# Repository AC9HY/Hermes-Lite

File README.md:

Hermes-Lite
===========

This fork is no loger being updated. The amplifers are now at https://github.com/W9JSW

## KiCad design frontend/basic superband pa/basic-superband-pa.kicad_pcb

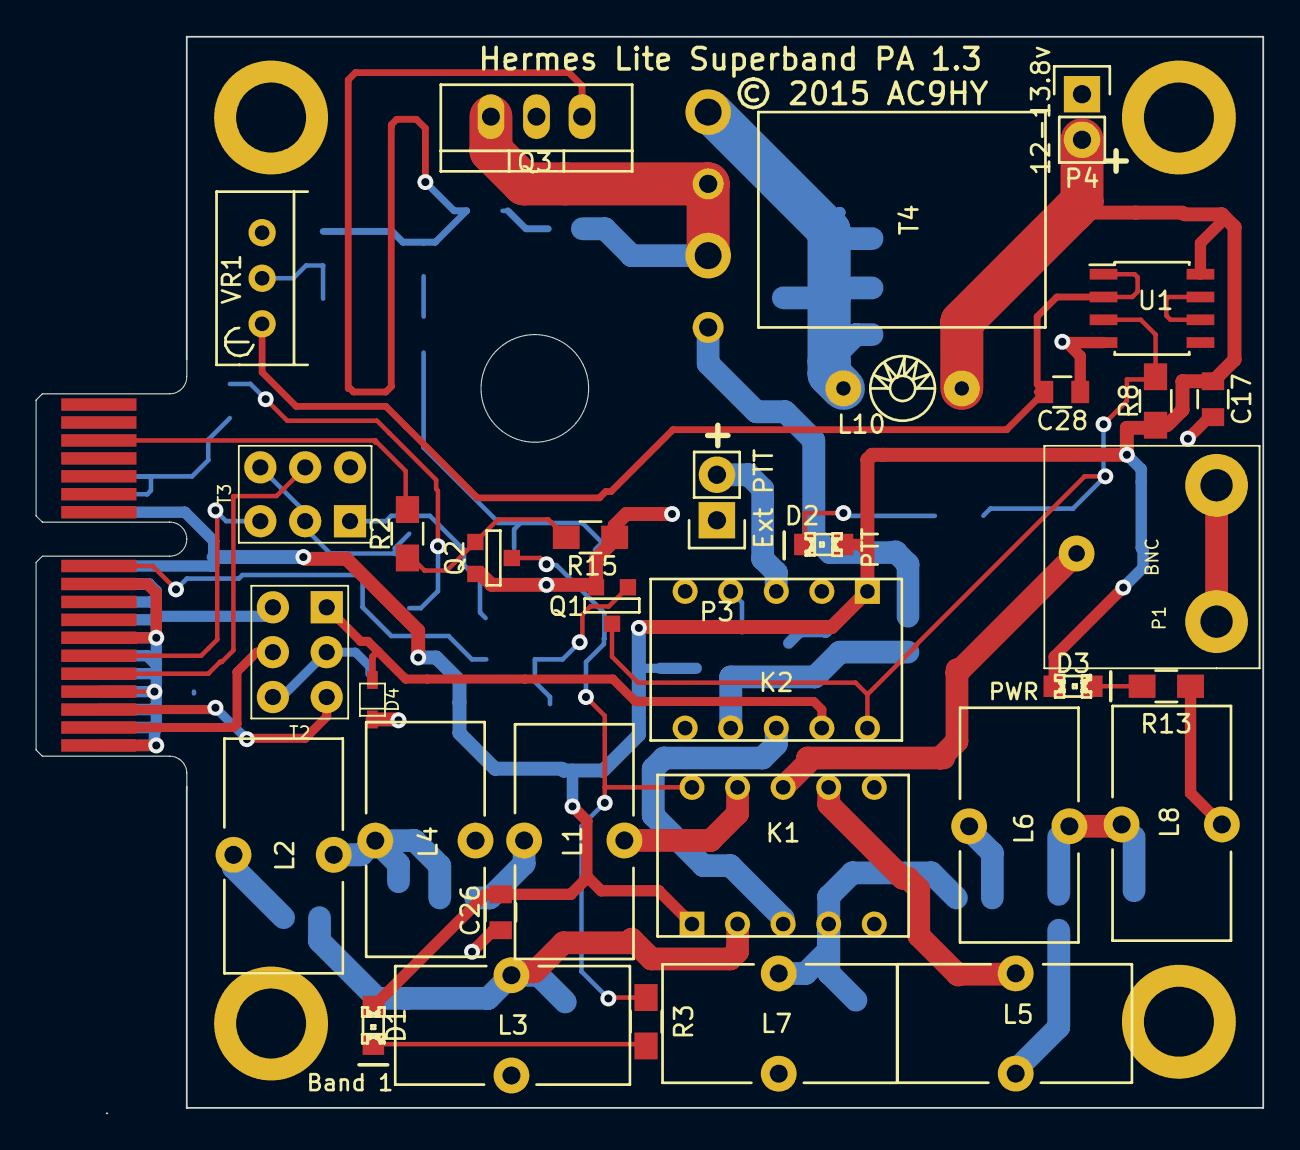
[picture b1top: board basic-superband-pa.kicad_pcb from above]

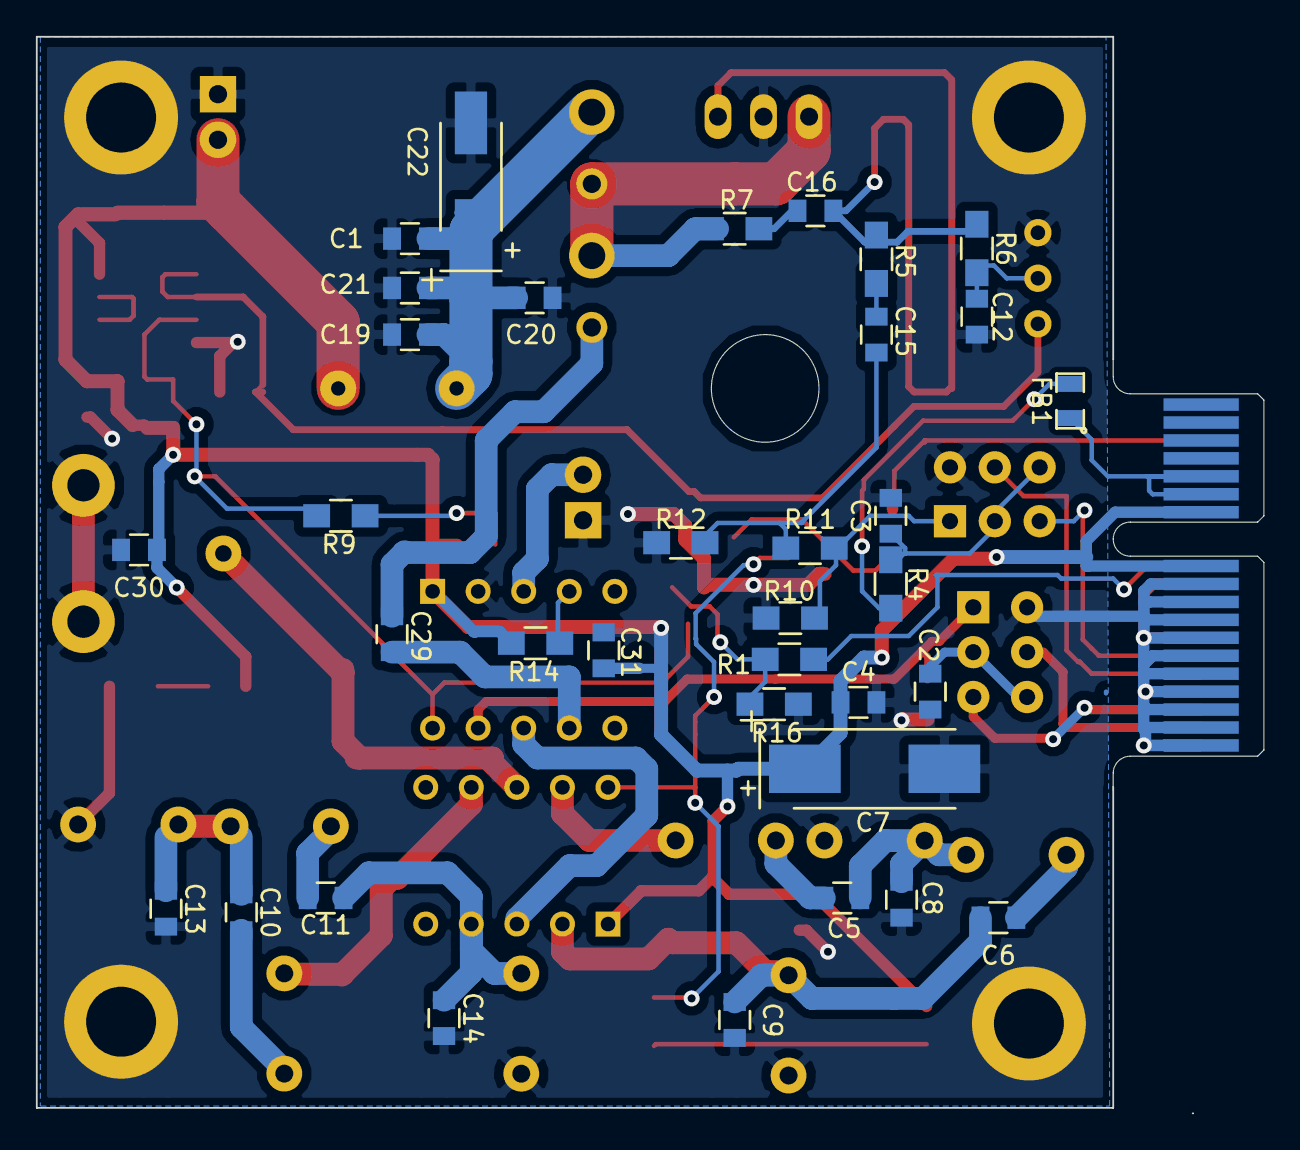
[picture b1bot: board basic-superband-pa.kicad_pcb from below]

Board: 2 copper layers, 68.4 x 59.7 mm, 75 parts (36 on the bottom side), 46 nets.

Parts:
C1, C4, C12, C15, C16, C19, C20, C26, C29, C30, C31: 0.1uF; C_0805
C2, C3: 0.1 uF; C_0805
C5, C6, C8, C9, C10, C11, C13, C14: C; C_0805
C7: 47uF 25V; TantalC_SizeD_EIA-7343_HandSoldering
C17, C28: 1uF; C_0805
C21: 4700pF; C_0805
C22: 10uF 25V; TantalC_SizeC_EIA-6032_HandSoldering
CN1: EDGE
D1: YEL LED (Band1); LED-0805
D2: RED LED (PTT); LED-0805
D3: GRN LED (PWR ON); LED-0805
D4: DIODESCH2; SOD323
FB1: FB; SMD-0805
K1, K2: D3002
L1, L2, L3, L4, L5, L6, L7, L8: INDUCTOR; Choke_Toroid_6,5x13mm_Vertical
L10: FT37-43 11T #26; Choke_Toroid_horizontal_Diameter3-5mm_Amidon-T12
MH: VAL**; MH
MH#2, MH#3, MH#4: VAL**; MH
MountingHole_6mm: VAL**; MountingHole_6mm
P1: BNC; BNCRA
P3: Ext PTT; Pin_Header_Straight_1x02
P4: 12-13.8v; Pin_Header_Straight_1x02
Q1, Q2: FDV301; SOT-23-GDS
Q3: RD16HHF1; TO-220_Neutral123_Vertical
R1, R2: 499; R_0805_HandSoldering
R3, R9, R13, R14: 4.99k; R_0805_HandSoldering
R4: 0; R_0805_HandSoldering
R5: 6.8; R_0805_HandSoldering
R6, R8, R15, R16: 10k; R_0805_HandSoldering
R7, R10, R12: 270; R_0805_HandSoldering
R11: 18; R_0805_HandSoldering
T2: 8:1; TRANSF
T3: 4:1; TRANSF
T4: OUT_TRANSF
U1: LP2951-50D; SOIC-8_3.9x4.9mm_Pitch1.27mm
VR1: 1k MT; Potentiometer_Bourns_3296W_3-8Zoll_Inline_ScrewUp

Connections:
/PTT: K2.10, Q1.D, R8.1, R9.1, U1.3
BAND1: K1.10, Q2.D, R3.1
GND: C1.1, C2.2, C3.2, C4.2, C7.2, C8.2, C9.2, C12.1, C13.2, C14.2, C17.2, C19.1, C20.1, C21.1, C22.2, C26.1, C28.1, C30.2, C31.2, CN1.A1, CN1.A2, CN1.A3, CN1.A4, CN1.A5, CN1.A6, CN1.A7, CN1.A8, CN1.A9, CN1.A10, CN1.B1, CN1.B4, CN1.B7, CN1.B10, D4.2, K2.2, L3.2, L4.2, L7.2, L8.2, P1.2, P3.1, P4.1, Q1.S, Q2.S, Q3.2, R10.1, R12.1, R13.1, R15.1, R16.1, T2.2, T3.2, U1.4, VR1.3
unnamed: C1.2, C19.2, C20.2, C21.2, C22.1, L10.2, T4.1
unnamed: C2.1, T2.3, T2.6
unnamed: C3.1, R4.1, T3.3, T3.6
unnamed: C5.1, L1.2
unnamed: C5.2, C8.1, L2.1, L4.1
unnamed: C6.1, L2.2
unnamed: C6.2, C9.1, K1.2, L3.1
unnamed: C10.1, C13.1, L6.2, L8.1
unnamed: C10.2, L5.1
unnamed: C11.1, C14.1, K1.4, L7.1
unnamed: C11.2, L6.1
unnamed: C12.2, R6.2, VR1.2
unnamed: C15.1, R5.2
unnamed: C15.2, R11.1, R12.2
unnamed: C16.1, R7.2
unnamed: C16.2, Q3.1, R5.1, R6.1
unnamed: C4.1, C7.1, C17.1, C26.2, C30.1, C31.1, CN1.A11, CN1.A12, D1.1, D2.1, D3.1, K1.1, K2.1, L10.1, P4.2, R8.2, R14.2, U1.8
unnamed: C28.2, U1.1, U1.2, VR1.1
unnamed: C29.1, K2.7
unnamed: C29.2, T4.4
unnamed: CN1.A13, CN1.A14, FB1.1
unnamed: CN1.B2, T2.4
unnamed: CN1.B3, T2.5
unnamed: CN1.B5, T3.4
unnamed: CN1.B6, T3.5
unnamed: D1.2, R3.2
unnamed: D2.2, R9.2
unnamed: D3.2, R13.2
unnamed: D4.1, K2.9, T2.1
unnamed: FB1.2, R4.2
unnamed: K1.3, K2.8
unnamed: K1.7, L5.2
unnamed: K1.8, P1.1
unnamed: K1.9, L1.1
unnamed: K2.3, P3.2
unnamed: K2.4, R14.1
unnamed: Q1.G, R1.1, R16.2
unnamed: Q2.G, R2.1, R15.2
unnamed: Q3.3, R7.1, T4.2, T4.3
unnamed: R10.2, R11.2, T3.1
unnamed: U1.6, U1.7
PTT: CN1.B11, R1.2
USEROUT4: CN1.B16, R2.2

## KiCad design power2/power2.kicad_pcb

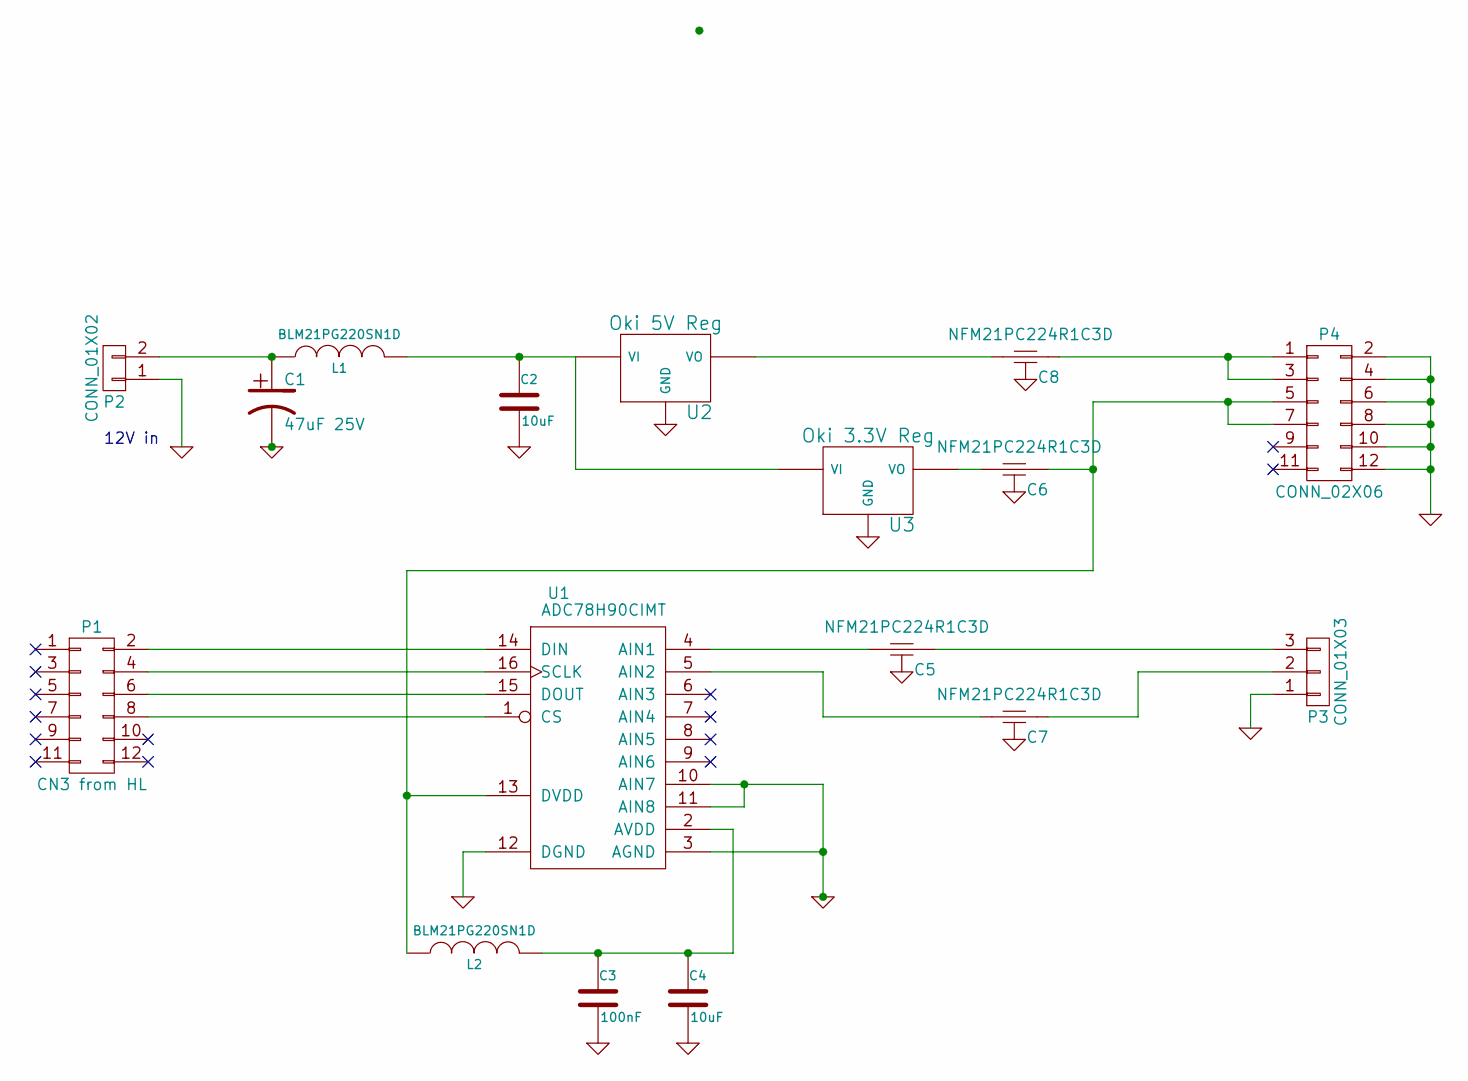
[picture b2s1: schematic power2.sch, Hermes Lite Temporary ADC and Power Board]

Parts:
C1: 47uF 25V; TantalC_SizeC_EIA-6032_HandSoldering
C2, C4: 10uF; C_0805_HandSoldering
C3: 100nF; C_0805_HandSoldering
C5, C6, C7, C8: NFM21PC224R1C3D; cfeed_0805
L1, L2: BLM21PG220SN1D; SMD-0805
P1: CN3 from HL; Socket_Strip_Angled_2x06
P2: CONN_01X02; Pin_Header_Straight_1x02
P3: CONN_01X03; Pin_Header_Straight_1x03
P4: CONN_02X06; Socket_Strip_Angled_2x06
U1: ADC78H90CIMT; SOIC-16_3.9x9.9mm_Pitch1.27mm
U2: Oki 5V Reg; LM78XXV
U3: Oki 3.3V Reg; LM78XXV

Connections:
GND: C1.2, C2.2, C3.2, C4.2, C5.3, C6.3, C7.3, C8.3, P2.1, P3.1, P4.2, P4.4, P4.6, P4.8, P4.10, P4.12, U1.3 (AGND), U1.10 (AIN7), U1.11 (AIN8), U1.12 (DGND), U2.GND, U3.GND; also elsewhere on the board
unnamed: C1.1, L1.1, P2.2
unnamed: C2.1, L1.2, U2.VI, U3.VI
unnamed: C3.1, C4.1, L2.2, U1.2 (AVDD)
unnamed: C5.1, U1.4 (AIN1)
unnamed: C5.2, P3.3
unnamed: C6.1, U3.VO
unnamed: C6.2, L2.1, P4.5, P4.7, U1.13 (DVDD)
unnamed: C7.1, U1.5 (AIN2)
unnamed: C7.2, P3.2
unnamed: C8.1, U2.VO
unnamed: C8.2, P4.1, P4.3
unnamed: P1.2, U1.14 (DIN)
unnamed: P1.4, U1.16 (SCLK)
unnamed: P1.6, U1.15 (DOUT)
unnamed: P1.8, U1.1 (CS)

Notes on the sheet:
12V in

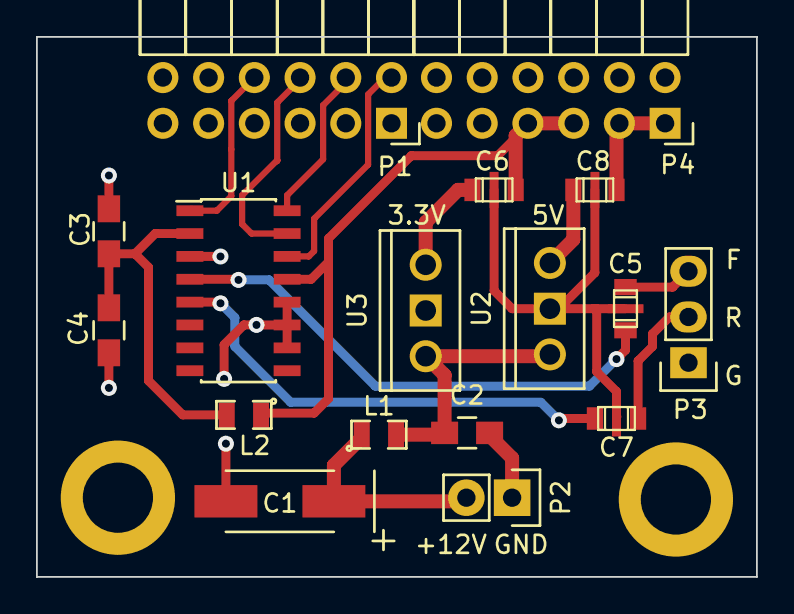
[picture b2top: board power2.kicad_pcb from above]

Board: 2 copper layers, 40.0 x 30.0 mm, 19 parts (0 on the bottom side), 16 nets.

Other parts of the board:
MH: VAL**; MH
MH#2: VAL**; MH

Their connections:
GND: MH.2, MH#2.1; also elsewhere on the board

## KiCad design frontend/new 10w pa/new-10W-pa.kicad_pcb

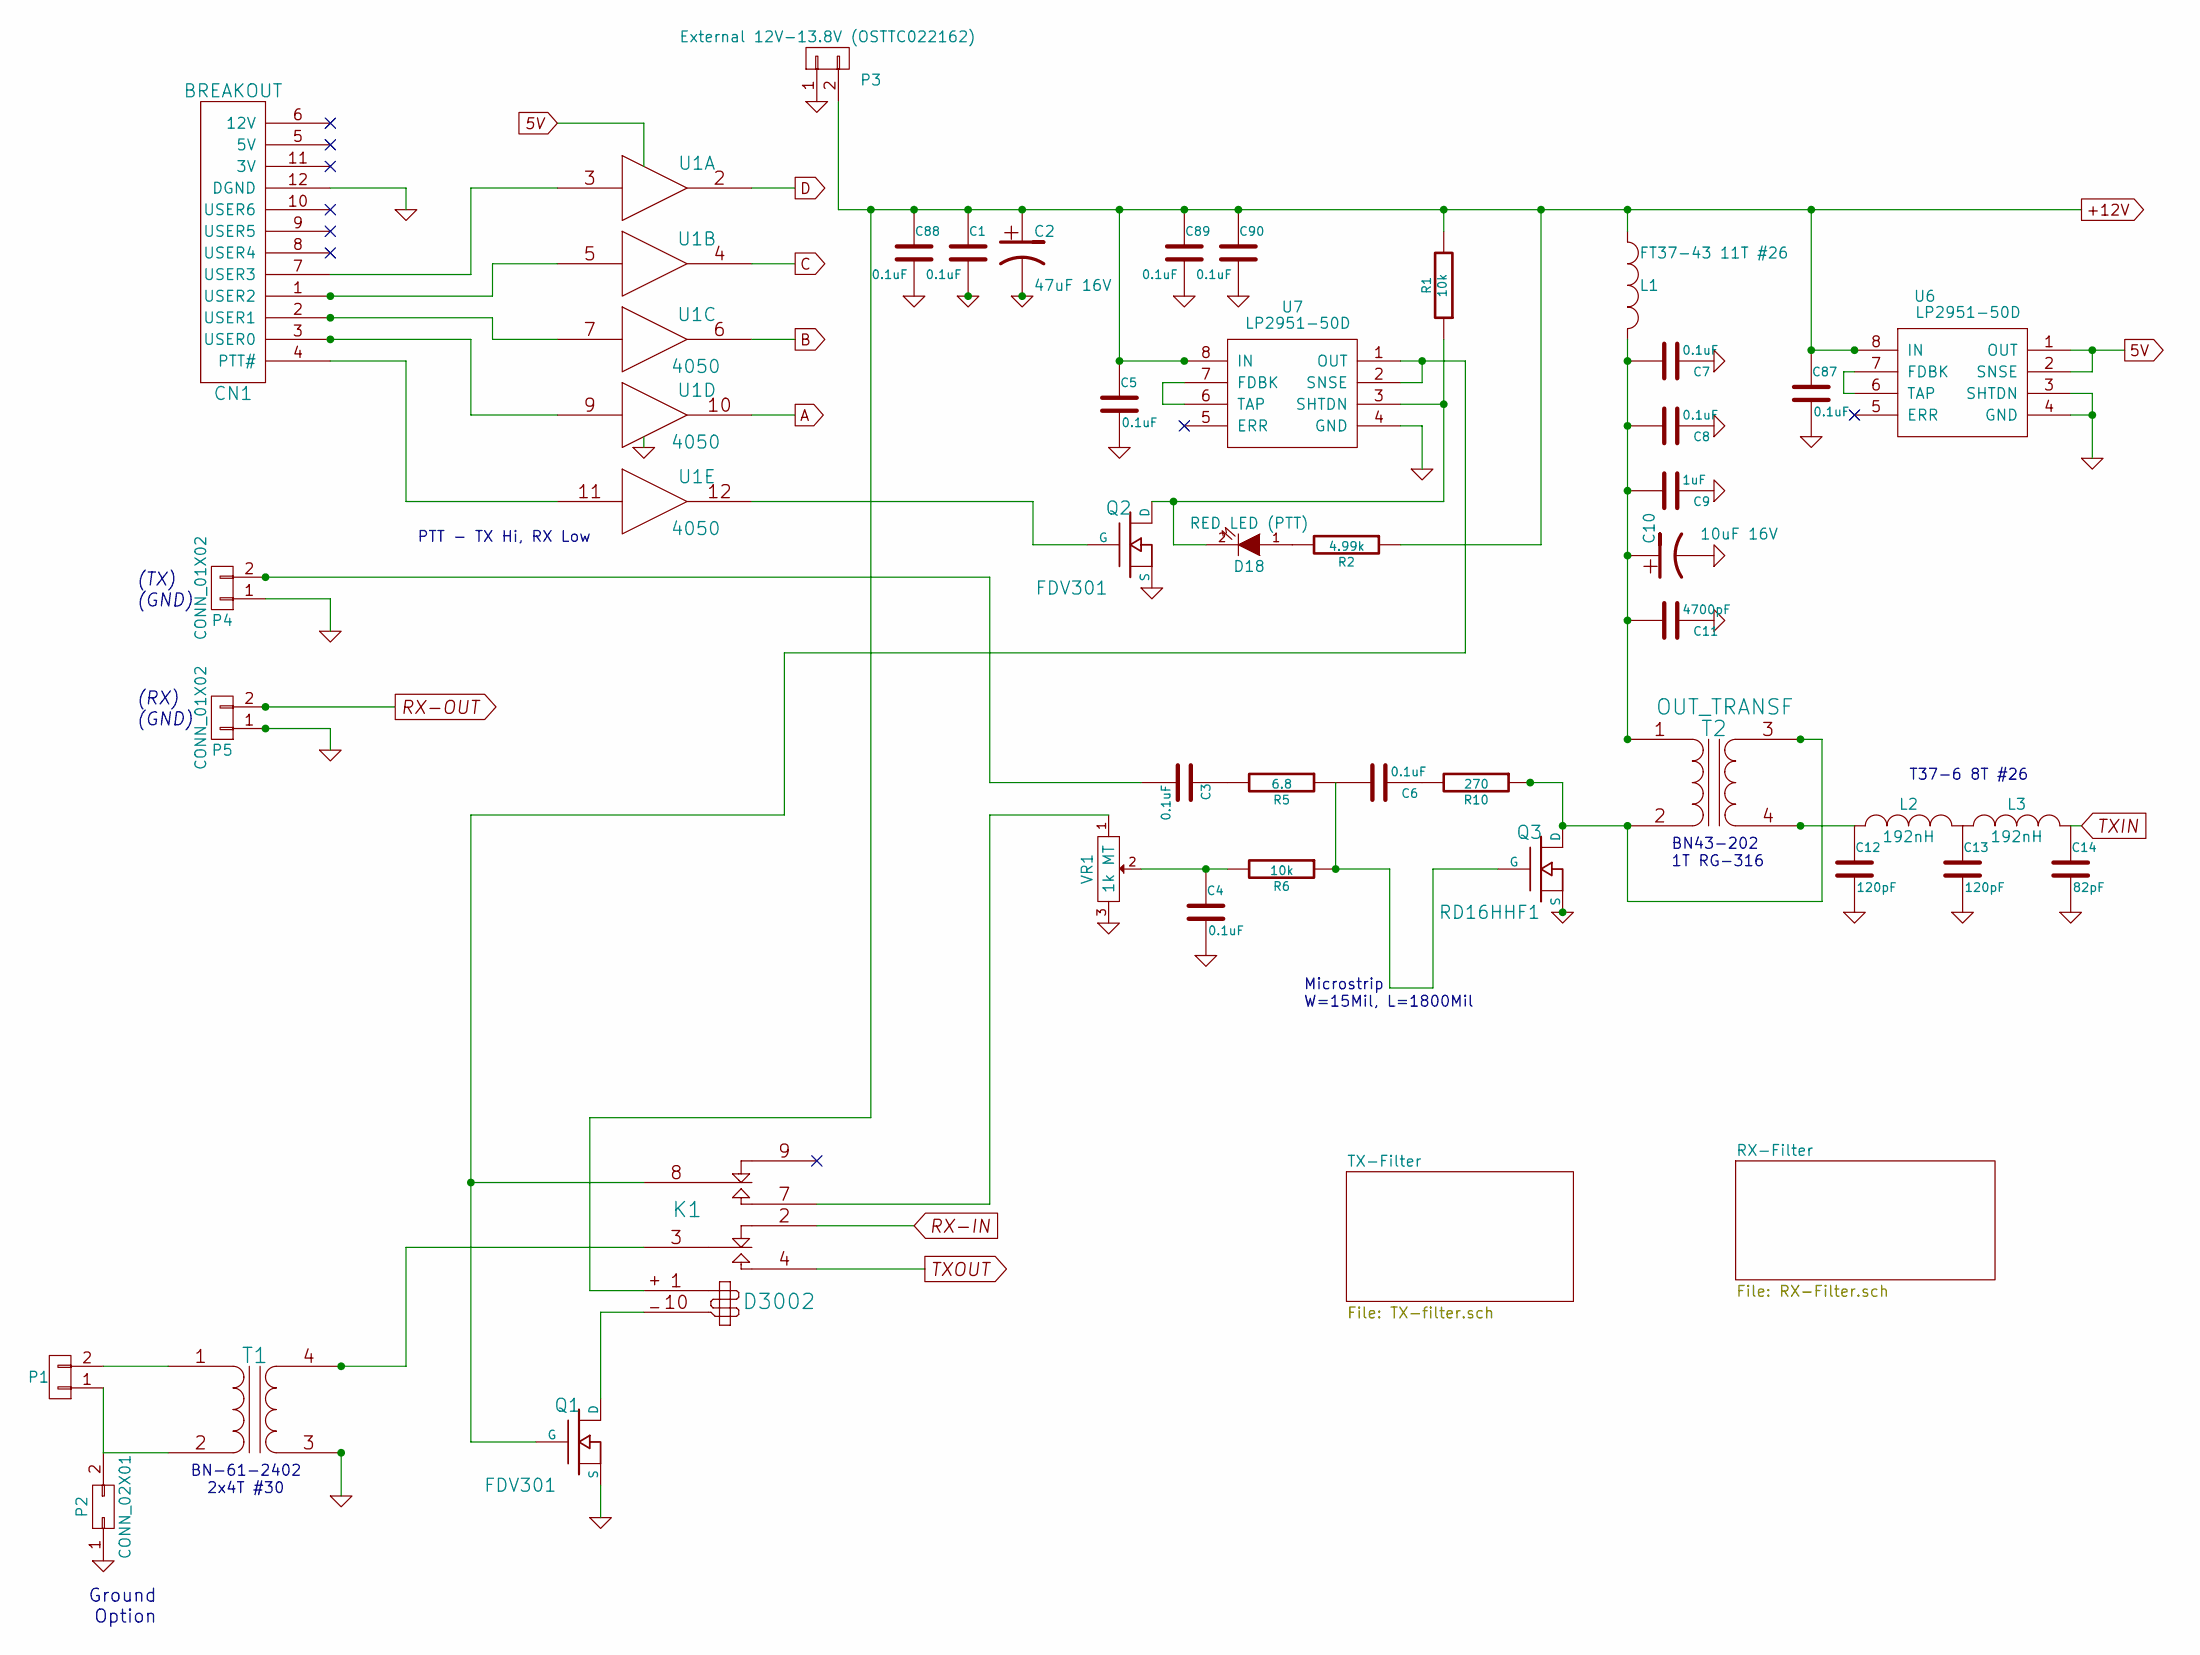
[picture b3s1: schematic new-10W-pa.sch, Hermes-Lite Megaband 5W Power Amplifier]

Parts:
C1, C3, C4, C5, C6, C7, C8, C87, C88, C89, C90: 0.1uF; C_0805
C2: 47uF 16V; TantalC_SizeD_EIA-7343_Reflow
C9: 1uF; C_0805
C10: 10uF 16V; TantalC_SizeB_EIA-3528_Reflow
C11: 4700pF; C_0805
C12, C13: 120pF; C_0805
C14: 82pF; C_0805
CN1: BREAKOUT
D18: RED LED (PTT); LED-0805
K1: D3002
L1: FT37-43 11T #26; Choke_Horizontal_RM10mm
L2, L3: 192nH; Choke_Toroid_6,5x13mm_Vertical
P1, P4, P5: CONN_01X02; Pin_Header_Straight_1x02
P2: CONN_02X01; Pin_Header_Straight_1x02
P3: External 12V-13.8V (OSTTC022162); AK300-2
Q1, Q2: FDV301; SOT-23-GDS
Q3: RD16HHF1; TO-220_Neutral123_Vertical_LargePads
R1, R6: 10k; R_0805
R2: 4.99k; R_0805
R5: 6.8; R_0805
R10: 270; R_0805
T1: TRANSFO; Socket_Strip_Straight_2x02
T2: OUT_TRANSF
U1: 4050; SOIC-16_3.9x9.9mm_Pitch1.27mm
U6, U7: LP2951-50D; SOIC-8_3.9x4.9mm_Pitch1.27mm
VR1: 1k MT; Potentiometer_Bourns_3296W_3-8Zoll_Inline_ScrewUp

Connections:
5V: U1.1 (VCC), U6.1 (OUT), U6.2 (SNSE); also elsewhere on the board
+12V: C1.1, C2.1, C5.1, C87.1, C88.1, C89.1, C90.1, K1.1 (+), L1.1, P3.2, R1.2, R2.1, U6.8 (IN), U7.8 (IN); also elsewhere on the board
A: U1.10; also elsewhere on the board
B: U1.6; also elsewhere on the board
C: U1.4; also elsewhere on the board
D: U1.2; also elsewhere on the board
unnamed: C3.1, R5.2
unnamed: C3.2, P4.2
unnamed: C4.1, R6.2, VR1.2
unnamed: C6.1, R10.2
unnamed: C6.2, Q3.1 (G), R5.1, R6.1
unnamed: C7.2, C8.2, C9.2, C10.1, C11.2, L1.2, T2.1 (AA)
unnamed: C12.1, L2.2, T2.4 (SA)
unnamed: C13.1, L2.1, L3.2
unnamed: CN1.1 (USER2), U1.5
unnamed: CN1.2 (USER1), U1.7
unnamed: CN1.3 (USER0), U1.9
unnamed: CN1.4 (PTT#), U1.11
unnamed: CN1.7 (USER3), U1.3
unnamed: D18.1 (A), R2.2
unnamed: D18.2 (K), Q2.D, R1.1, U7.3 (SHTDN)
unnamed: K1.3 (C1), T1.4 (SB)
unnamed: K1.7 (T2), VR1.1
unnamed: K1.8 (C2), Q1.G, U7.1 (OUT), U7.2 (SNSE)
unnamed: K1.10 (-), Q1.D
unnamed: P1.1, P2.2, T1.2 (AB)
unnamed: P1.2, T1.1 (AA)
unnamed: Q2.G, U1.12
unnamed: Q3.3 (D), R10.1, T2.2 (AB), T2.3 (SB)
unnamed: U6.6 (TAP), U6.7 (FDBK)
unnamed: U7.6 (TAP), U7.7 (FDBK)
RX-IN: K1.2 (R1); also elsewhere on the board
RX-OUT: P5.2; also elsewhere on the board
TXIN: C14.1, L3.1; also elsewhere on the board
TXOUT: K1.4 (T1); also elsewhere on the board
VSS: C1.2, C2.2, C4.2, C5.2, C7.1, C8.1, C9.1, C10.2, C11.1, C12.2, C13.2, C14.2, C87.2, C88.2, C89.2, C90.2, CN1.12 (DGND), P2.1, P3.1, P4.1, P5.1, Q1.S, Q2.S, Q3.2 (S), T1.3 (SA), U1.8 (VSS), U6.3 (SHTDN), U6.4 (GND), U7.4 (GND), VR1.3; also elsewhere on the board

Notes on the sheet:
Ground Option
BN-61-2402 2x4T #30
BN43-202 1T RG-316
(TX) (GND)
(RX) (GND)
T37-6 8T #26
Microstrip W=15Mil, L=1800Mil
PTT - TX Hi, RX Low

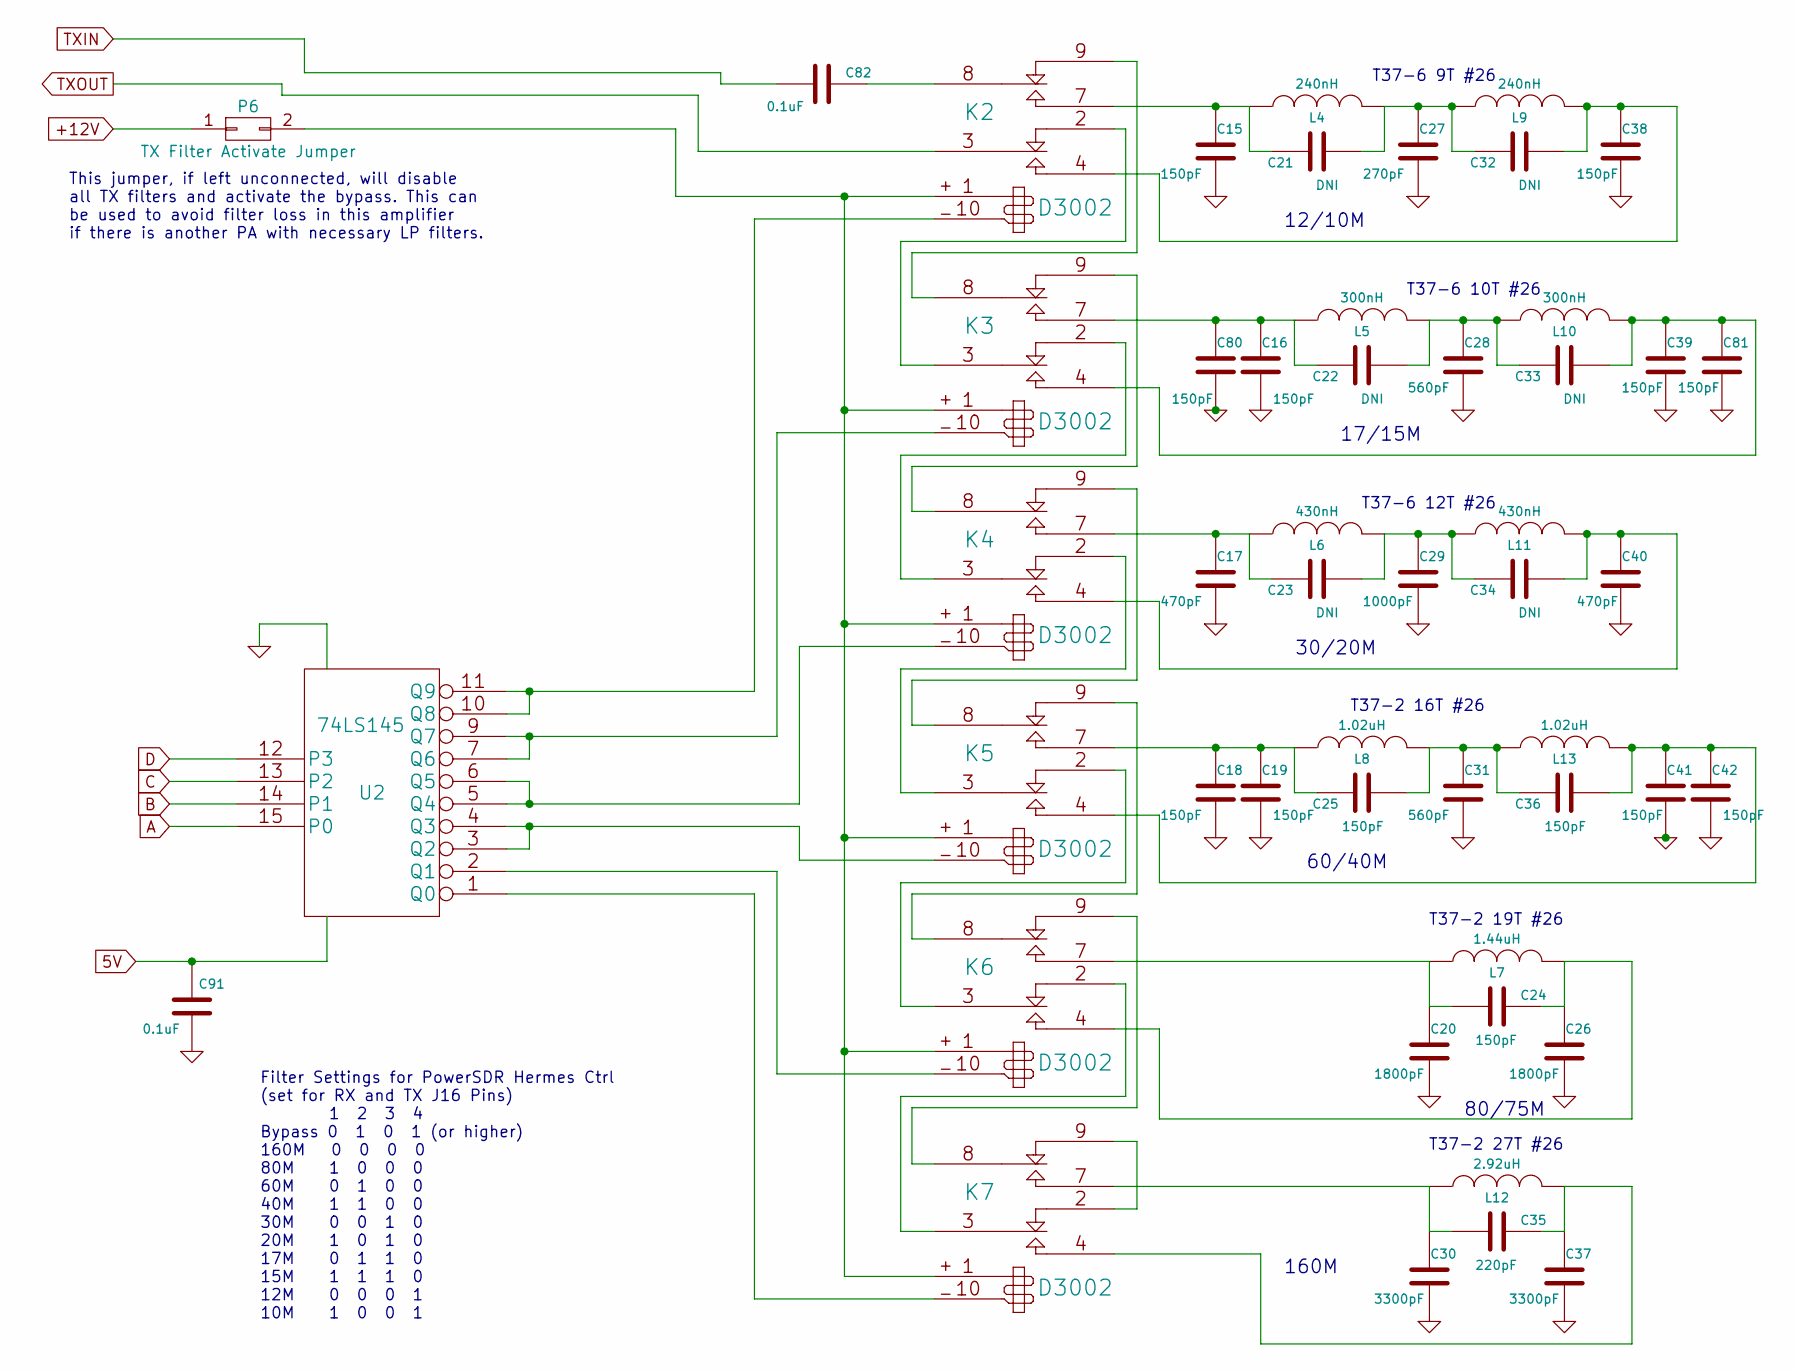
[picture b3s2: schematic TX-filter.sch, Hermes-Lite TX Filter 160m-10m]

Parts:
C15, C16, C18, C19, C24, C25, C36, C38, C39, C41, C42, C80, C81: 150pF; C_0805
C17, C40: 470pF; C_0805
C20, C26: 1800pF; C_0805
C21, C22, C23, C32, C33, C34: DNI; C_0805
C27: 270pF; C_0805
C28, C31: 560pF; C_0805
C29: 1000pF; C_0805
C30, C37: 3300pF; C_0805
C35: 220pF; C_0805
C82, C91: 0.1uF; C_0805
K2, K3, K4, K5, K6, K7: D3002
L4, L9: 240nH; Choke_Toroid_6,5x13mm_Vertical
L5, L10: 300nH; Choke_Toroid_6,5x13mm_Vertical
L6, L11: 430nH; Choke_Toroid_6,5x13mm_Vertical
L7: 1.44uH; Choke_Toroid_6,5x13mm_Vertical
L8, L13: 1.02uH; Choke_Toroid_6,5x13mm_Vertical
L12: 2.92uH; Choke_Toroid_6,5x13mm_Vertical
P6: TX Filter Activate Jumper; Pin_Header_Straight_1x02
U2: 74LS145; SOIC-16_3.9x9.9mm_Pitch1.27mm

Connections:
5V: C91.2, U2.16 (VCC); also elsewhere on the board
+12V: P6.1; also elsewhere on the board
A: U2.15 (P0); also elsewhere on the board
B: U2.14 (P1); also elsewhere on the board
C: U2.13 (P2); also elsewhere on the board
D: U2.12 (P3); also elsewhere on the board
unnamed: C15.1, C21.1, K2.7 (T2), L4.1
unnamed: C16.1, C22.1, C80.1, K3.7 (T2), L5.1
unnamed: C17.1, C23.1, K4.7 (T2), L6.1
unnamed: C18.1, C19.1, C25.1, K5.7 (T2), L8.1
unnamed: C20.1, C24.2, K6.7 (T2), L7.1
unnamed: C21.2, C27.1, C32.1, L4.2, L9.1
unnamed: C22.2, C28.1, C33.1, L5.2, L10.1
unnamed: C23.2, C29.1, C34.1, L6.2, L11.1
unnamed: C24.1, C26.1, K6.4 (T1), L7.2
unnamed: C25.2, C31.1, C36.1, L8.2, L13.1
unnamed: C30.1, C35.2, K7.7 (T2), L12.1
unnamed: C32.2, C38.1, K2.4 (T1), L9.2
unnamed: C33.2, C39.1, C81.1, K3.4 (T1), L10.2
unnamed: C34.2, C40.1, K4.4 (T1), L11.2
unnamed: C35.1, C37.1, K7.4 (T1), L12.2
unnamed: C36.2, C41.1, C42.1, K5.4 (T1), L13.2
unnamed: C82.1, K2.8 (C2)
unnamed: K2.1 (+), K3.1 (+), K4.1 (+), K5.1 (+), K6.1 (+), K7.1 (+), P6.2
unnamed: K2.2 (R1), K3.3 (C1)
unnamed: K2.9 (R2), K3.8 (C2)
unnamed: K2.10 (-), U2.10 (Q8), U2.11 (Q9)
unnamed: K3.2 (R1), K4.3 (C1)
unnamed: K3.9 (R2), K4.8 (C2)
unnamed: K3.10 (-), U2.7 (Q6), U2.9 (Q7)
unnamed: K4.2 (R1), K5.3 (C1)
unnamed: K4.9 (R2), K5.8 (C2)
unnamed: K4.10 (-), U2.5 (Q4), U2.6 (Q5)
unnamed: K5.2 (R1), K6.3 (C1)
unnamed: K5.9 (R2), K6.8 (C2)
unnamed: K5.10 (-), U2.3 (Q2), U2.4 (Q3)
unnamed: K6.2 (R1), K7.3 (C1)
unnamed: K6.9 (R2), K7.8 (C2)
unnamed: K6.10 (-), U2.2 (Q1)
unnamed: K7.2 (R1), K7.9 (R2)
unnamed: K7.10 (-), U2.1 (Q0)
TXIN: C82.2; also elsewhere on the board
TXOUT: K2.3 (C1); also elsewhere on the board
VSS: C15.2, C16.2, C17.2, C18.2, C19.2, C20.2, C26.2, C27.2, C28.2, C29.2, C30.2, C31.2, C37.2, C38.2, C39.2, C40.2, C41.2, C42.2, C80.2, C81.2, C91.1, U2.8 (GND); also elsewhere on the board

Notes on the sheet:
160M
60/40M
80/75M
T37-2 16T #26
T37-2 19T #26
T37-2 27T #26
30/20M
T37-6 12T #26
17/15M
T37-6 10T #26
12/10M
T37-6 9T #26
Filter Settings for PowerSDR Hermes Ctrl (set for RX and TX J16 Pins) 1 2 3 4 Bypass 0 1 0 1 (or higher) 160M 0 0 0 0 80M 1 0 0 0 60M 0 1 0 0 40M 1 1 0 0 30M 0 0 1 0 20M 1 0 1 0 17M 0 1 1 0 15M 1 1 1 0 12M 0 0 0 1 10M 1 0 0 1
This jumper, if left unconnected, will disable all TX filters and activate the bypass. This can be used to avoid filter loss in this amplifier if there is another PA with necessary LP filters.

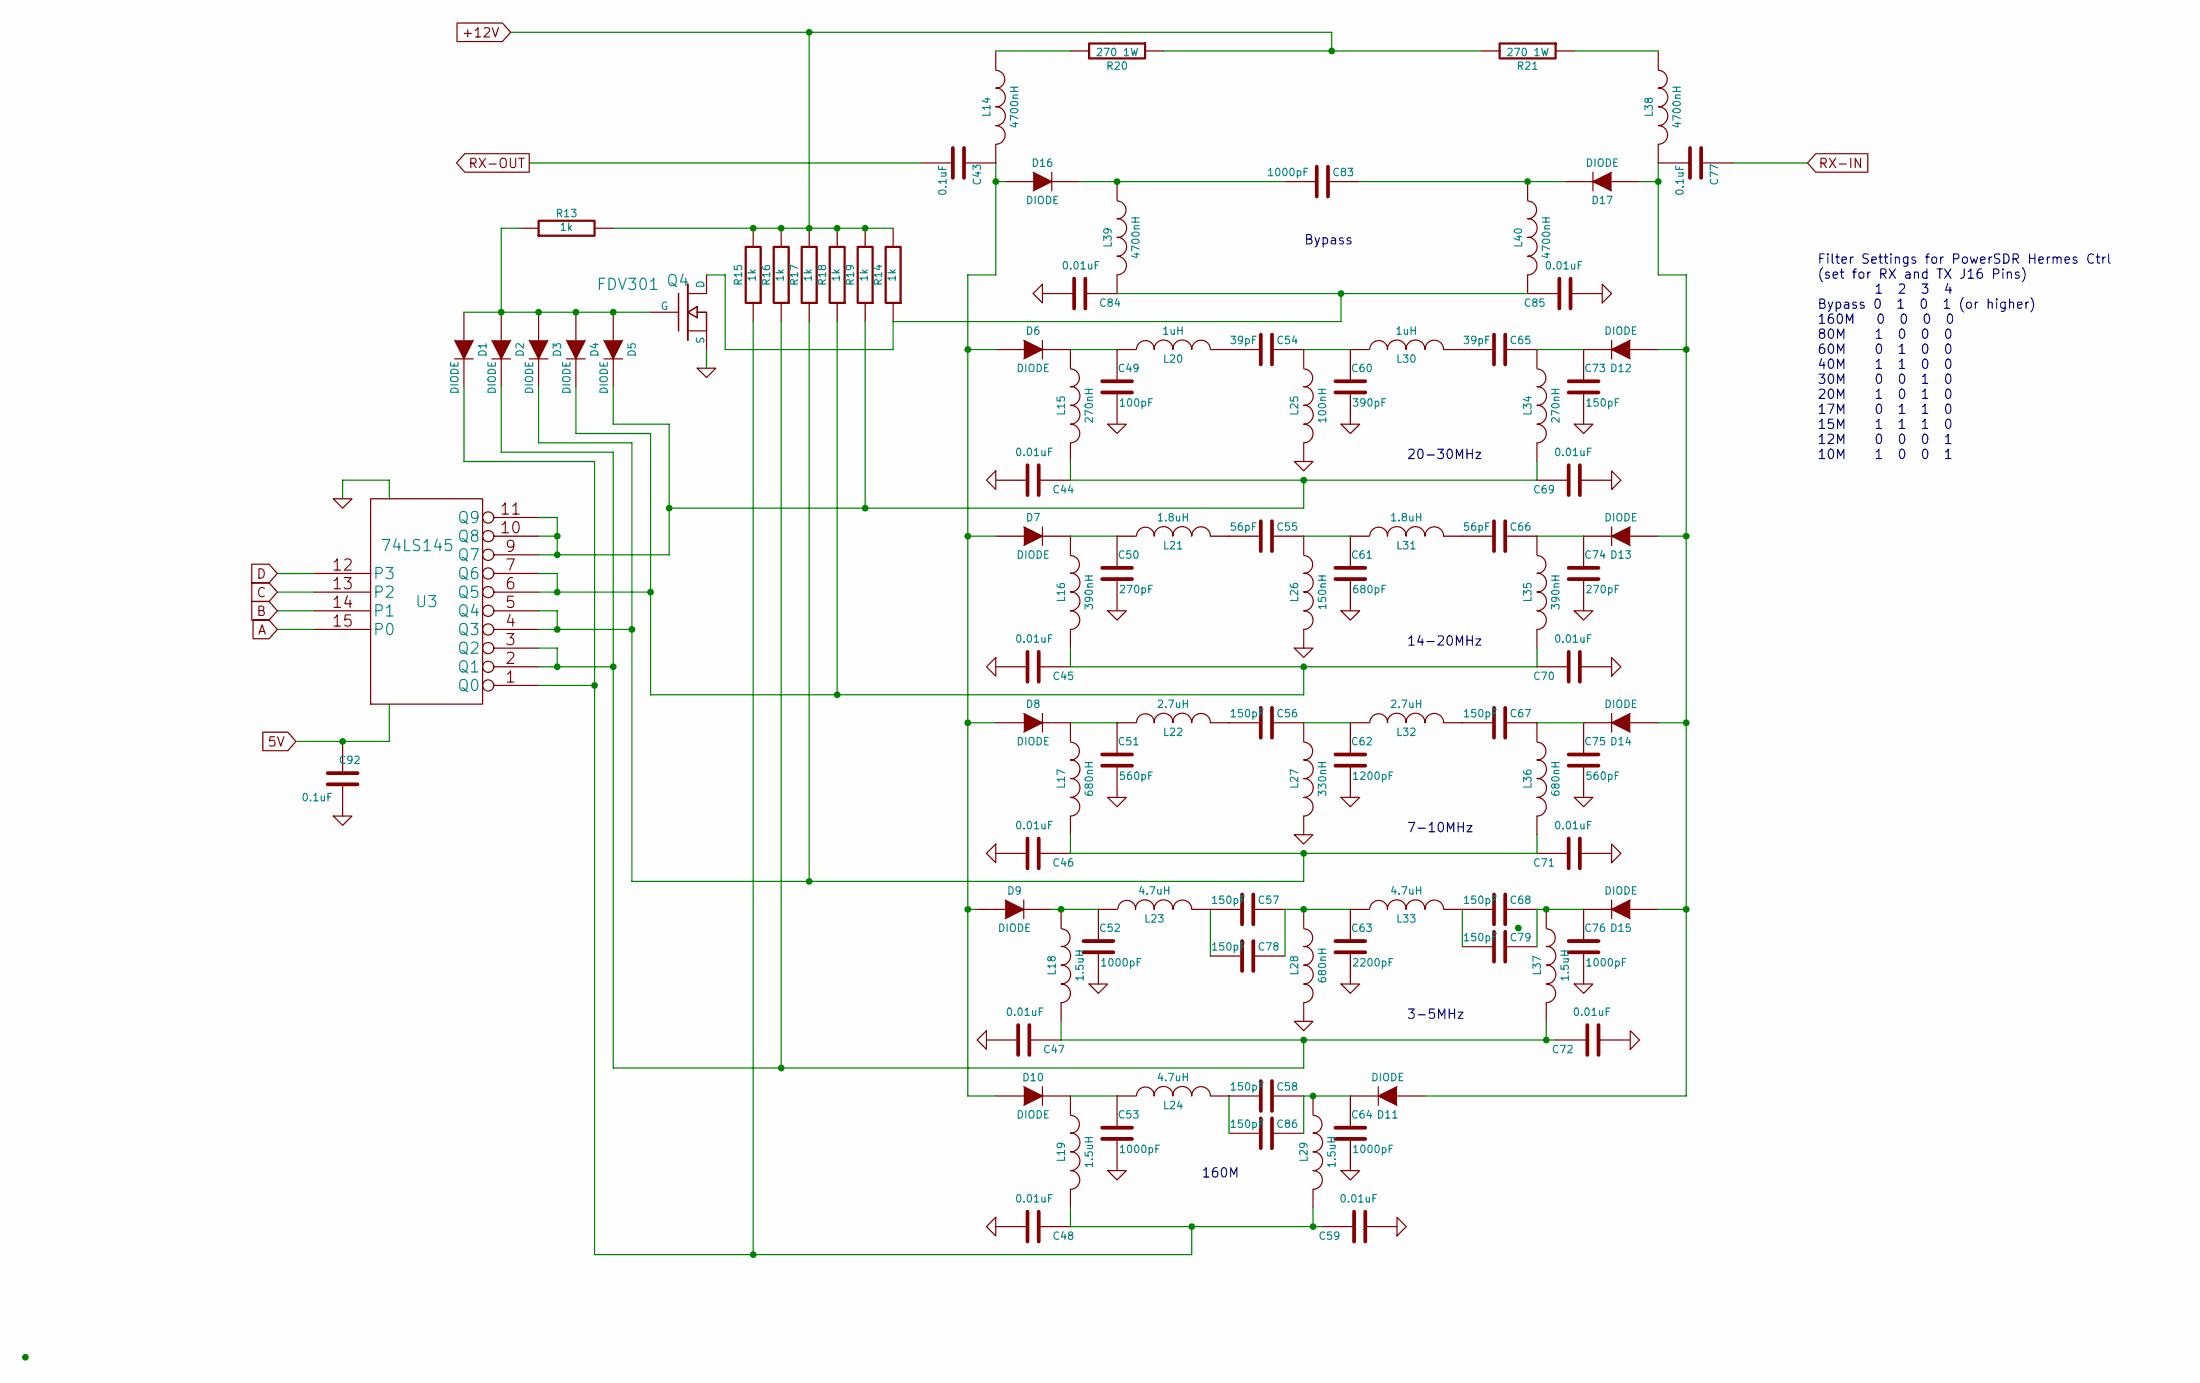
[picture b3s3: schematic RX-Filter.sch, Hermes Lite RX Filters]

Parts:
C43, C77, C92: 0.1uF; C_0805
C44, C45, C46, C47, C48, C59, C69, C70, C71, C72, C84, C85: 0.01uF; C_0805
C49: 100pF; C_0805
C50, C74: 270pF; C_0805
C51, C75: 560pF; C_0805
C52, C53, C64, C76, C83: 1000pF; C_0805
C54, C65: 39pF; C_0805
C55, C66: 56pF; C_0805
C56, C57, C58, C67, C68, C73, C78, C79, C86: 150pF; C_0805
C60: 390pF; C_0805
C61: 680pF; C_0805
C62: 1200pF; C_0805
C63: 2200pF; C_0805
D1, D2, D3, D4, D5, D6, D7, D8, D9, D10, D11, D12, D13, D14, D15, D16, D17: DIODE; Diode-SMA_Standard
L14, L38, L39, L40: 4700nH; Choke_SMD_1206_Standard
L15, L34: 270nH; Choke_SMD_1206_Standard
L16, L35: 390nH; Choke_SMD_1206_Standard
L17, L28, L36: 680nH; Choke_SMD_1206_Standard
L18, L19, L29, L37: 1.5uH; Choke_SMD_1206_Standard
L20, L30: 1uH; Choke_SMD_1206_Standard
L21, L31: 1.8uH; Choke_SMD_1206_Standard
L22, L32: 2.7uH; Choke_SMD_1206_Standard
L23, L24, L33: 4.7uH; Choke_SMD_1206_Standard
L25: 100nH; Choke_SMD_1206_Standard
L26: 150nH; Choke_SMD_1206_Standard
L27: 330nH; Choke_SMD_1206_Standard
Q4: FDV301; SOT-23-GDS
R13, R14, R15, R16, R17, R18, R19: 1k; R_0805
R20, R21: 270 1W; Resistor_Vertical_RM5mm
U3: 74LS145; SOIC-16_3.9x9.9mm_Pitch1.27mm

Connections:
5V: C92.2, U3.16 (VCC); also elsewhere on the board
+12V: R13.2, R14.2, R15.2, R16.2, R17.2, R18.2, R19.2, R20.1, R21.2; also elsewhere on the board
A: U3.15 (P0); also elsewhere on the board
B: U3.14 (P1); also elsewhere on the board
C: U3.13 (P2); also elsewhere on the board
D: U3.12 (P3); also elsewhere on the board
unnamed: C43.1, D6.1 (A), D7.1 (A), D8.1 (A), D9.1 (A), D10.1 (A), D16.1 (A), L14.2
unnamed: C44.1, C69.1, D5.2 (K), L15.2, L34.2, R19.1, U3.9 (Q7), U3.10 (Q8), U3.11 (Q9)
unnamed: C45.1, C70.1, D4.2 (K), L16.2, L35.2, R18.1, U3.6 (Q5), U3.7 (Q6)
unnamed: C46.1, C71.1, D3.2 (K), L17.2, L36.2, R17.1, U3.4 (Q3), U3.5 (Q4)
unnamed: C47.1, C72.1, D2.2 (K), L18.2, L37.2, R16.1, U3.2 (Q1), U3.3 (Q2)
unnamed: C48.1, C59.1, D1.2 (K), L19.2, L29.2, R15.1, U3.1 (Q0)
unnamed: C49.1, D6.2 (K), L15.1, L20.1
unnamed: C50.1, D7.2 (K), L16.1, L21.1
unnamed: C51.1, D8.2 (K), L17.1, L22.1
unnamed: C52.1, D9.2 (K), L18.1, L23.1
unnamed: C53.1, D10.2 (K), L19.1, L24.1
unnamed: C54.1, C60.1, L25.1, L30.1
unnamed: C54.2, L20.2
unnamed: C55.1, C61.1, L26.1, L31.1
unnamed: C55.2, L21.2
unnamed: C56.1, C62.1, L27.1, L32.1
unnamed: C56.2, L22.2
unnamed: C57.1, C63.1, C78.1, L28.1, L33.1
unnamed: C57.2, C78.2, L23.2
unnamed: C58.1, C64.1, C86.1, D11.2 (K), L29.1
unnamed: C58.2, C86.2, L24.2
unnamed: C65.1, C73.1, D12.2 (K), L34.1
unnamed: C65.2, L30.2
unnamed: C66.1, C74.1, D13.2 (K), L35.1
unnamed: C66.2, L31.2
unnamed: C67.1, C75.1, D14.2 (K), L36.1
unnamed: C67.2, L32.2
unnamed: C68.1, C76.1, C79.1, D15.2 (K), L37.1
unnamed: C68.2, C79.2, L33.2
unnamed: C77.2, D11.1 (A), D12.1 (A), D13.1 (A), D14.1 (A), D15.1 (A), D17.1 (A), L38.2
unnamed: C83.1, D17.2 (K), L40.1
unnamed: C83.2, D16.2 (K), L39.1
unnamed: C84.1, C85.1, L39.2, L40.2, Q4.D, R14.1
unnamed: D1.1 (A), D2.1 (A), D3.1 (A), D4.1 (A), D5.1 (A), Q4.G, R13.1
unnamed: L14.1, R20.2
unnamed: L38.1, R21.1
RX-IN: C77.1; also elsewhere on the board
RX-OUT: C43.2; also elsewhere on the board
VSS: C44.2, C45.2, C46.2, C47.2, C48.2, C49.2, C50.2, C51.2, C52.2, C53.2, C59.2, C60.2, C61.2, C62.2, C63.2, C64.2, C69.2, C70.2, C71.2, C72.2, C73.2, C74.2, C75.2, C76.2, C84.2, C85.2, C92.1, L25.2, L26.2, L27.2, L28.2, Q4.S, U3.8 (GND); also elsewhere on the board

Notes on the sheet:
20-30MHz
7-10MHz
14-20MHz
3-5MHz
160M
Filter Settings for PowerSDR Hermes Ctrl (set for RX and TX J16 Pins) 1 2 3 4 Bypass 0 1 0 1 (or higher) 160M 0 0 0 0 80M 1 0 0 0 60M 0 1 0 0 40M 1 1 0 0 30M 0 0 1 0 20M 1 0 1 0 17M 0 1 1 0 15M 1 1 1 0 12M 0 0 0 1 10M 1 0 0 1
Bypass

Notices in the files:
frontend/basic superband pa/basic-superband-pa.kicad_pcb:
© 2015 AC9HY
frontend/new 10w pa/new-10W-pa.kicad_pcb:
© AC9HY/WA2EUJ 2015 Ver 1.2
power1/power1.kicad_pcb:
© 2015 AC9HY ver 1.0
